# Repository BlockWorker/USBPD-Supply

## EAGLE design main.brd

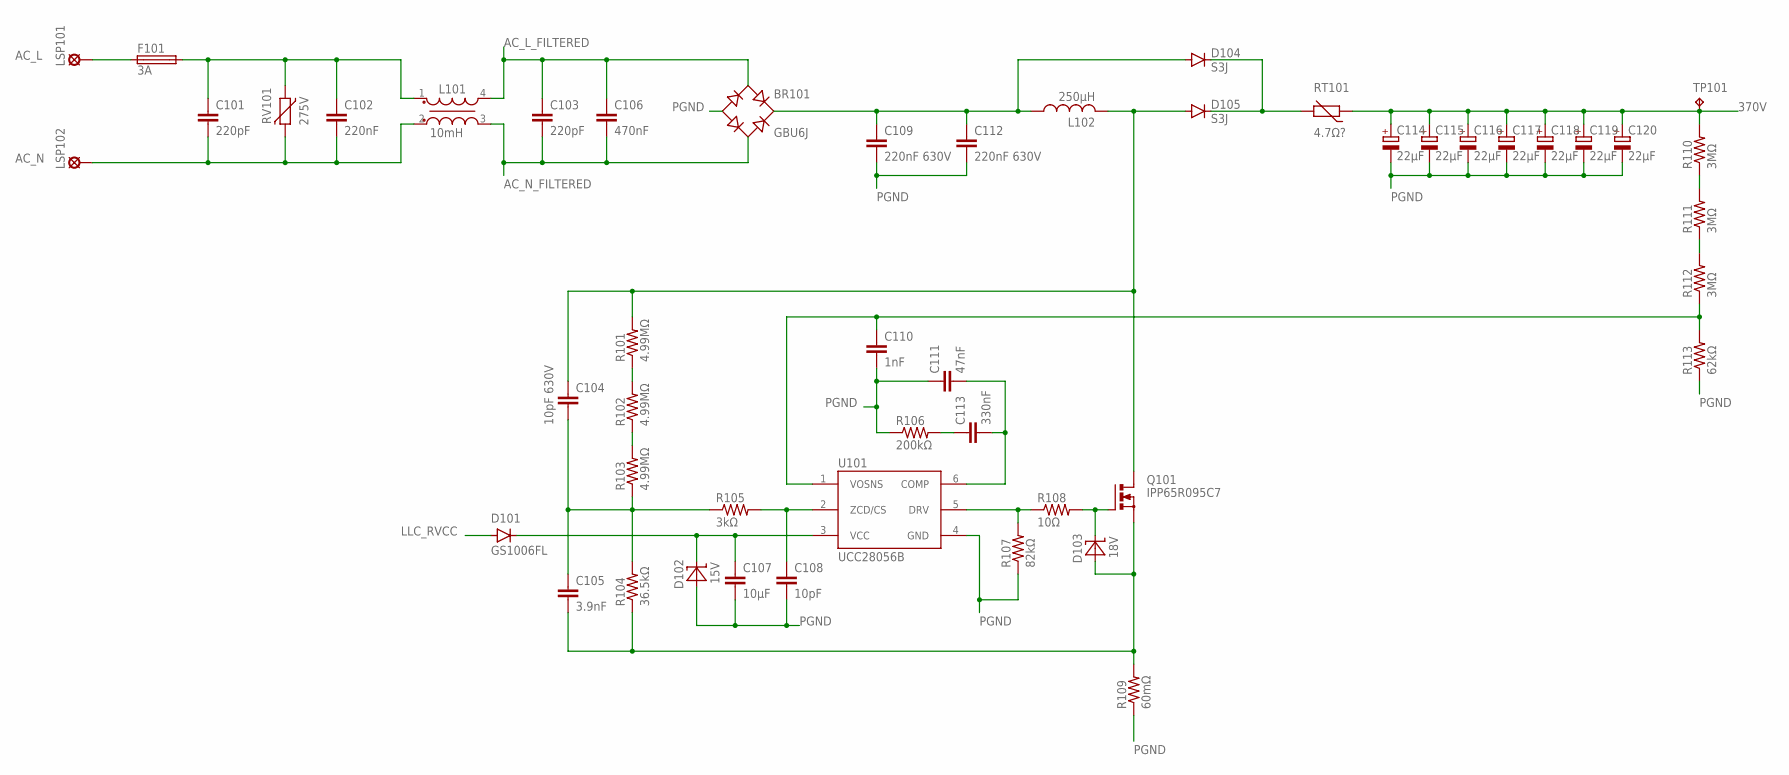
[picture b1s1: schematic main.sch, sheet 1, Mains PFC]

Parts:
BR101: GBU6J; GBU6
C101, C103: 220pF; C-10MM-TH
C102: 220nF; WCAP-FTX2-220N
C104: 10pF 630V; C1206
C105: 3.9nF; C0603
C106: 470nF; WCAP-FTX2-470N
C107: 10µF; C0805
C108: 10pF; C0603
C109, C112: 220nF 630V; C1812
C110: 1nF; C0603
C111: 47nF; C0603
C113: 330nF; C0603
C114, C115, C116, C117, C118, C119, C120: 22µF; E5-12.5
D101: GS1006FL; SOD123FL
D102: 15V; SOD123
D103: 18V; SOD123
D104, D105: S3J; SMC
F101: 3A; MRF_FUSE
L101: 10mH; WE-CMB_M
L102: 250µH; ATCA-08
LSP101: AC_L; LSP13
LSP102: AC_N; LSP13
Q101: IPP65R095C7; TO220BV-HS1
R101, R102, R103: 4.99MΩ; R1206
R104: 36.5kΩ; R0603
R105: 3kΩ; R0603
R106: 200kΩ; R0603
R107: 82kΩ; R0603
R108: 10Ω; R0603
R109: 60mΩ; R1206
R110, R111, R112: 3MΩ; R1206
R113: 62kΩ; R0603
RT101: 4.7Ω?; R-5
RV101: 275V; B72207S0271
TP101: RCU-0(J); TP_0603_JOINED
U101: UCC28056B; SOT23-6L

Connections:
370V: C114.+, C115.+, C116.+, C117.+, C118.+, C119.+, C120.+, R110.2, RT101.1, TP101.1; also elsewhere on the board
AC_L: F101.1, LSP101.MP
AC_L_FILTERED: BR101.2 (AC1), C103.1, C106.1, L101.4; also elsewhere on the board
AC_L_FUSED: C101.1, C102.1, F101.2, L101.1, RV101.1
AC_N: C101.2, C102.2, L101.2, LSP102.MP, RV101.2
AC_N_FILTERED: BR101.3 (AC2), C103.2, C106.2, L101.3; also elsewhere on the board
AC_RECTIFIED: BR101.4 (+), C109.1, C112.1, D104.A, L102.1
LLC_RVCC: D101.A; also elsewhere on the board
PFC_COMP: C111.2, C113.2, U101.6 (COMP)
PFC_COMP_INT: C113.1, R106.2
PFC_CS: C105.2, D103.A, Q101.S, R104.1, R109.2
PFC_DRV: R107.2, R108.1, U101.5 (DRV)
PFC_DRV_R: D103.C, Q101.G, R108.2
PFC_OUT_RAW: D104.C, D105.C, RT101.2
PFC_SW_NODE: C104.1, D105.A, L102.2, Q101.D, R101.2
PFC_VCC: C107.1, D101.C, D102.C, U101.3 (VCC)
PFC_VOSNS: C110.1, R112.1, R113.2, U101.1 (VOSNS)
PFC_VOSNS_RB: R111.1, R112.2
PFC_VOSNS_RT: R110.1, R111.2
PFC_ZCD/CS: C108.1, R105.2, U101.2 (ZCD/CS)
PFC_ZCD/CS_RAW: C104.2, C105.1, R103.1, R104.2, R105.1
PFC_ZCD_RB: R102.1, R103.2
PFC_ZCD_RT: R101.1, R102.2
PGND: BR101.1 (-), C107.2, C108.2, C109.2, C110.2, C111.1, C112.2, C114.-, C115.-, C116.-, C117.-, C118.-, C119.-, C120.-, D102.A, R106.1, R107.1, R109.1, R113.1, U101.4 (GND); also elsewhere on the board

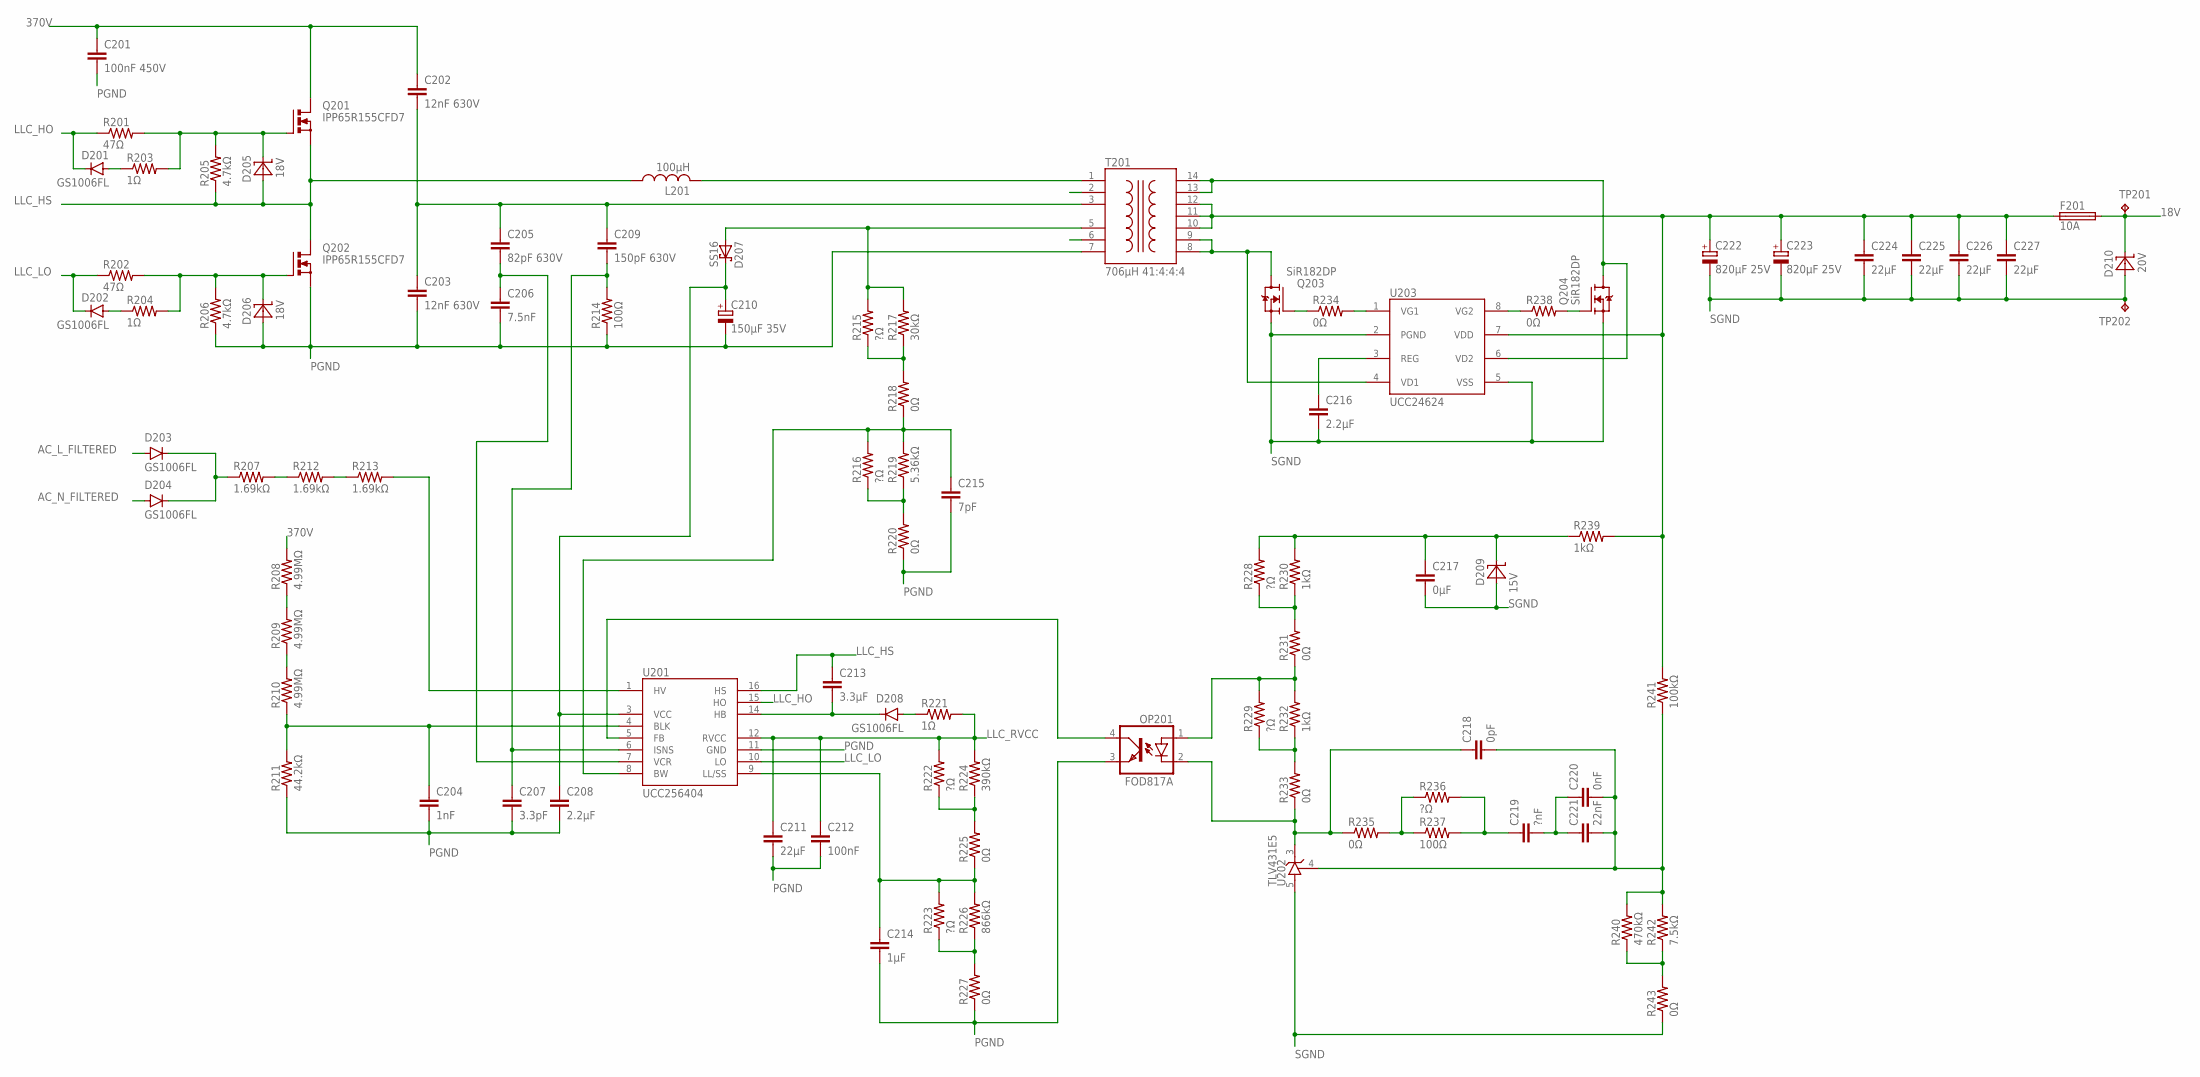
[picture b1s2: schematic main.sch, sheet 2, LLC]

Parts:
C201: 100nF 450V; C1206
C202, C203: 12nF 630V; C1210
C204: 1nF; C0603
C205: 82pF 630V; C1206
C206: 7.5nF; C0603
C207: 3.3pF; C0603
C208, C216: 2.2µF; C0805
C209: 150pF 630V; C1206
C210: 150µF 35V; PANASONIC_E
C211, C224, C225, C226, C227: 22µF; C0805
C212: 100nF; C0603
C213: 3.3µF; C0805
C214: 1µF; C0603
C215: 7pF; C0603
C217: 0µF; C0603
C218: 0pF; C0603
C219: ?nF; C0603
C220: 0nF; C0603
C221: 22nF; C0603
C222, C223: 820µF 25V; E5-10,5
D201, D202, D203, D204, D208: GS1006FL; SOD123FL
D205, D206: 18V; SOD123
D207: SS16; DO-214AC
D209: 15V; SOD123
D210: 20V; SOD123
F201: 10A; MRF_FUSE
L201: 100µH; HCTI-1MM
OP201: FOD817A; DIP4
Q201, Q202: IPP65R155CFD7; TO220BV-HS1
Q203, Q204: SiR182DP; POWERPAK-SO8
R201, R202: 47Ω; R0603
R203, R204, R221: 1Ω; R0603
R205, R206: 4.7kΩ; R0603
R207, R212, R213: 1.69kΩ; R1206
R208, R209, R210: 4.99MΩ; R1206
R211: 44.2kΩ; R0603
R214: 100Ω; R1206
R215, R216, R222, R223, R228, R229, R236: ?Ω; R0603
R217: 30kΩ; R0603
R218, R220, R225, R227, R231, R233, R234, R235, R238, R243: 0Ω; R0603
R219: 5.36kΩ; R0603
R224: 390kΩ; R0603
R226: 866kΩ; R0603
R230, R232, R239: 1kΩ; R0603
R237: 100Ω; R0603
R240: 470kΩ; R0603
R241: 100kΩ; R0603
R242: 7.5kΩ; R0603
T201: 706µH 41:4:4:4; ETD29/16/10-H
TP201, TP202: RCU-0(J); TP_0603_JOINED
U201: UCC256404; SOIC16-NO2,13
U202: TLV431E5; SOT23-5L
U203: UCC24624; SOIC8

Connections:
18V: D210.C, F201.2, TP201.1; also elsewhere on the board
370V: C201.1, C202.1, Q201.D, R208.2; also elsewhere on the board
AC_L_FILTERED: D203.A; also elsewhere on the board
AC_N_FILTERED: D204.A; also elsewhere on the board
LLC_AUX: D207.A, R215.2, R217.2, T201.5
LLC_BLK: C204.1, R210.1, R211.2, U201.4 (BLK)
LLC_BLK_RB: R209.1, R210.2
LLC_BLK_RT: R208.1, R209.2
LLC_BW: C215.1, R216.2, R218.1, R219.2, U201.8 (BW)
LLC_BW_RB: R216.1, R219.1, R220.2
LLC_BW_RT: R215.1, R217.1, R218.2
LLC_FB: OP201.4 (COL), U201.5 (FB)
LLC_FB_COMP: C219.1, R236.2, R237.2
LLC_FB_COMPC: C219.2, C220.1, C221.1
LLC_FB_COMPR: R235.2, R236.1, R237.1
LLC_FB_OPA: OP201.1 (A), R229.2, R231.1, R232.2
LLC_FB_OPAP: C217.1, D209.C, R228.2, R230.2, R239.1
LLC_FB_OPAR: R228.1, R230.1, R231.2
LLC_FB_OPBR: R229.1, R232.1, R233.2
LLC_FB_OPK: C218.1, OP201.2 (C), R233.1, R235.1, U202.3 (C)
LLC_FB_VREF: C218.2, C220.2, C221.2, R240.2, R241.1, R242.2, U202.4 (R)
LLC_FB_VREFR: R240.1, R242.1, R243.2
LLC_HB: C213.2, D208.C, U201.14 (HB)
LLC_HB_FEED: D208.A, R221.1
LLC_HO: D201.C, R201.1, U201.15 (HO)
LLC_HO_DIS: D201.A, R203.1
LLC_HO_R: D205.C, Q201.G, R201.2, R203.2, R205.2
LLC_HS: C213.1, D205.A, L201.1, Q201.S, Q202.D, R205.1, U201.16 (HS)
LLC_HV: R213.2, U201.1 (HV)
LLC_HV_RB: R212.2, R213.1
LLC_HV_RECT: D203.C, D204.C, R207.1
LLC_HV_RT: R207.2, R212.1
LLC_ISNS: C207.1, C209.2, R214.2, U201.6 (ISNS)
LLC_LL/SS: C214.1, R223.2, R225.1, R226.2, U201.9 (LL/SS)
LLC_LL_RB: R223.1, R226.1, R227.2
LLC_LL_RT: R222.1, R224.1, R225.2
LLC_LO: D202.C, R202.1, U201.10 (LO)
LLC_LO_DIS: D202.A, R204.1
LLC_LO_R: D206.C, Q202.G, R202.2, R204.2, R206.2
LLC_OUT: C222.+, C223.+, C224.1, C225.1, C226.1, C227.1, F201.1, R239.2, R241.2, T201.10, T201.11, T201.12, U203.7 (VDD)
LLC_PRI_IN: L201.2, T201.1
LLC_PRI_OUT: C202.2, C203.1, C205.1, C209.1, T201.3
LLC_RVCC: C211.1, C212.1, R221.2, R222.2, R224.2, U201.12 (RVCC); also elsewhere on the board
LLC_SR_REG: C216.1, U203.3 (REG)
LLC_SR_VD1: Q203.5-8 (D), T201.8, T201.9, U203.4 (VD1)
LLC_SR_VD2: Q204.5-8 (D), T201.13, T201.14, U203.6 (VD2)
LLC_SR_VG1: R234.2, U203.1 (VG1)
LLC_SR_VG1_R: Q203.4 (G), R234.1
LLC_SR_VG2: R238.1, U203.8 (VG2)
LLC_SR_VG2_R: Q204.4 (G), R238.2
LLC_VCC: C208.1, C210.+, D207.C, U201.3 (VCC)
LLC_VCR: C205.2, C206.1, U201.7 (VCR)
PGND: C201.2, C203.2, C204.2, C206.2, C207.2, C208.2, C210.-, C211.2, C212.2, C214.2, C215.2, D206.A, OP201.3 (EMIT), Q202.S, R206.1, R211.1, R214.1, R220.1, R227.1, T201.7, U201.11 (GND); also elsewhere on the board
PRI_DUMMY_1: T201.2
PRI_DUMMY_2: T201.6
SGND: C216.2, C217.2, C222.-, C223.-, C224.2, C225.2, C226.2, C227.2, D209.A, D210.A, Q203.1 (S), Q203.2 (S), Q203.3 (S), Q204.1 (S), Q204.2 (S), Q204.3 (S), R243.1, TP202.1, U202.5 (A), U203.2 (PGND), U203.5 (VSS); also elsewhere on the board

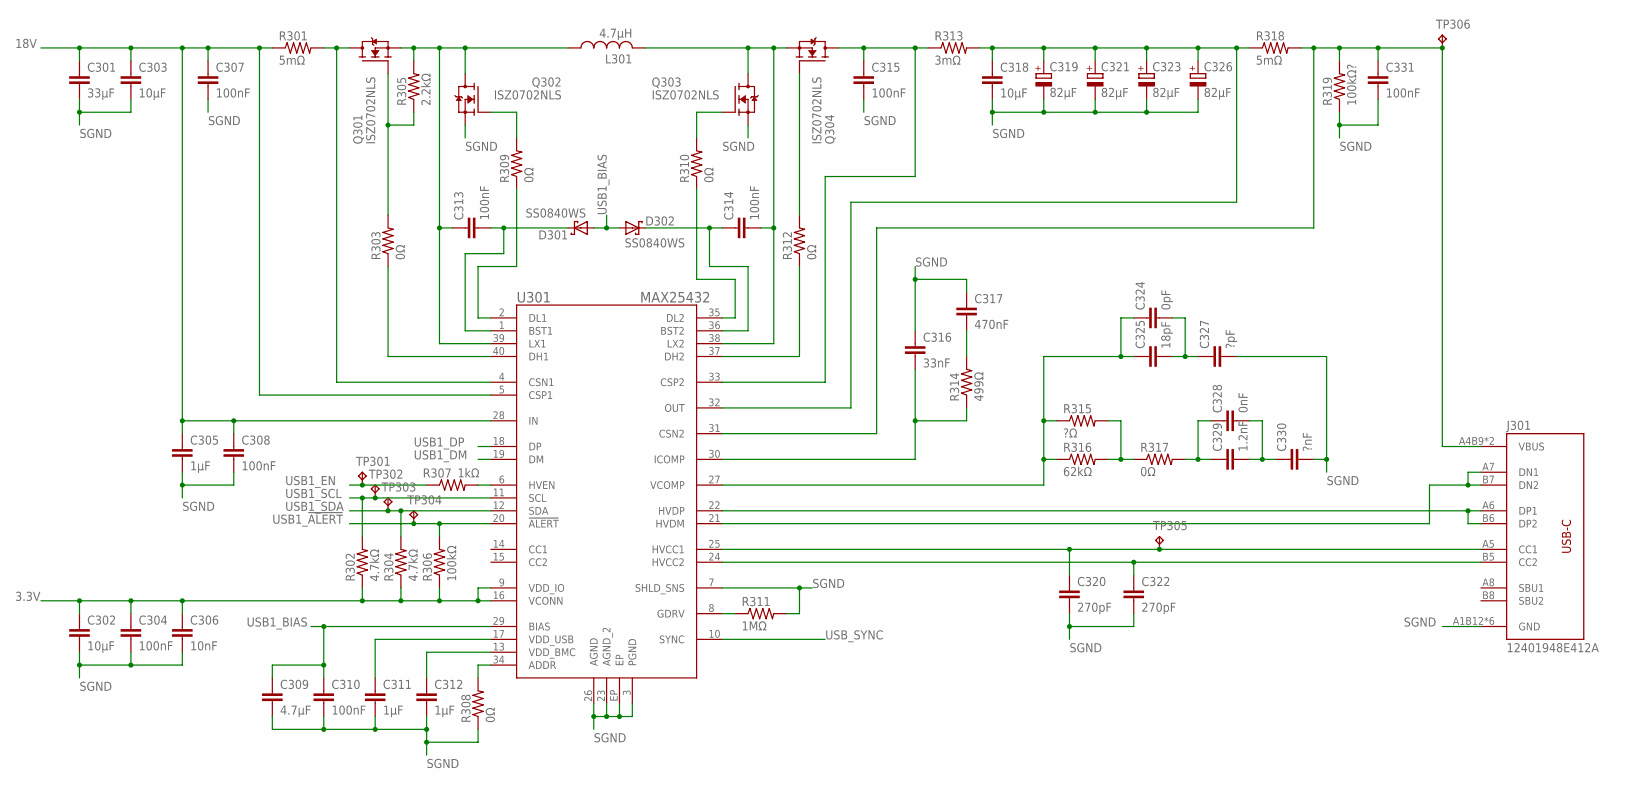
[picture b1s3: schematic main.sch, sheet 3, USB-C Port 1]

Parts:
C301: 33µF; C1206
C302, C303, C318: 10µF; C0805
C304, C307, C308, C310, C313, C314, C315, C331: 100nF; C0603
C305, C311, C312: 1µF; C0603
C306: 10nF; C0603
C309: 4.7µF; C0603
C316: 33nF; C0603
C317: 470nF; C0603
C319, C321, C323, C326: 82µF; E3,5-8
C320, C322: 270pF; C0603
C324: 0pF; C0603
C325: 18pF; C0603
C327: ?pF; C0603
C328: 0nF; C0603
C329: 1.2nF; C0603
C330: ?nF; C0603
D301, D302: SS0840WS; SOD323
J301: 12401948E412A
L301: 4.7µH; B82559B*A016
Q301, Q302, Q303, Q304: ISZ0702NLS; TSDSON-8
R301, R318: 5mΩ; R0805
R302, R304: 4.7kΩ; R0603
R303, R308, R309, R310, R312, R317: 0Ω; R0603
R305: 2.2kΩ; R0603
R306: 100kΩ; R0603
R307: 1kΩ; R0603
R311: 1MΩ; R0603
R313: 3mΩ; R0805
R314: 499Ω; R0603
R315: ?Ω; R0603
R316: 62kΩ; R0603
R319: 100kΩ?; R0603
TP301, TP302, TP303, TP304, TP305, TP306: RCU-0(J); TP_0603_JOINED
U301: MAX25432; TQFN-40

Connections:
3.3V: C302.1, C304.1, C306.1, R302.1, R304.1, R306.1, U301.9 (VDD_IO), U301.16 (VCONN); also elsewhere on the board
18V: C301.1, C303.1, C305.1, C307.1, C308.1, R301.1, U301.5 (CSP1), U301.28 (IN); also elsewhere on the board
SGND: C301.2, C302.2, C303.2, C304.2, C305.2, C306.2, C307.2, C308.2, C309.2, C310.2, C311.2, C312.2, C315.2, C316.1, C317.1, C318.2, C319.-, C320.2, C321.-, C322.2, C323.-, C326.-, C327.2, C330.2, C331.2, J301.A1B12 (GND), J301.B1A12 (GND), J301.M1 (GND), J301.M2 (GND), J301.M3 (GND), J301.M4 (GND), Q302.1 (S), Q302.2 (S), Q302.3 (S), Q303.1 (S), Q303.2 (S), Q303.3 (S), R308.1, R311.2, R319.1, U301.3 (PGND), U301.7 (SHLD_SNS), U301.23 (AGND_2), U301.26 (AGND), U301.EP; also elsewhere on the board
USB1_!ALERT: R306.2, TP304.1, U301.20 (!ALERT); also elsewhere on the board
USB1_ADDR: R308.2, U301.34 (ADDR)
USB1_BIAS: C309.1, C310.1, D301.2 (A), D302.2 (A), U301.29 (BIAS)
USB1_BST1: C313.2, D301.1 (C), U301.1 (BST1)
USB1_BST2: C314.1, D302.1 (C), U301.36 (BST2)
USB1_CC1: C320.1, J301.A5 (CC1), TP305.1, U301.25 (HVCC1)
USB1_CC2: C322.1, J301.B5 (CC2), U301.24 (HVCC2)
USB1_CSN1: Q301.5-8 (D), R301.2, U301.4 (CSN1)
USB1_CSP2: C315.1, Q304.5-8 (D), R313.1, U301.33 (CSP2)
USB1_DH1: R303.1, U301.40 (DH1)
USB1_DH1_R: Q301.4 (G), R303.2, R305.1
USB1_DH2: R312.1, U301.37 (DH2)
USB1_DH2_R: Q304.4 (G), R312.2
USB1_DL1: R309.1, U301.2 (DL1)
USB1_DL1_R: Q302.4 (G), R309.2
USB1_DL2: R310.1, U301.35 (DL2)
USB1_DL2_R: Q303.4 (G), R310.2
USB1_DM: U301.19 (DM); also elsewhere on the board
USB1_DP: U301.18 (DP); also elsewhere on the board
USB1_EN: R307.1, TP301.1; also elsewhere on the board
USB1_GDRV: R311.1, U301.8 (GDRV)
USB1_HVDM: J301.A7 (DN1), J301.B7 (DN2), U301.21 (HVDM)
USB1_HVDP: J301.A6 (DP1), J301.B6 (DP2), U301.22 (HVDP)
USB1_HVEN: R307.2, U301.6 (HVEN)
USB1_ICOMP: C316.2, R314.1, U301.30 (ICOMP)
USB1_ICOMP_R: C317.2, R314.2
USB1_LX1: C313.1, L301.1, Q301.1 (S), Q301.2 (S), Q301.3 (S), Q302.5-8 (D), R305.2, U301.39 (LX1)
USB1_LX2: C314.2, L301.2, Q303.5-8 (D), Q304.1 (S), Q304.2 (S), Q304.3 (S), U301.38 (LX2)
USB1_OUT: C318.1, C319.+, C321.+, C323.+, C326.+, R313.2, R318.1, U301.32 (OUT)
USB1_SCL: R302.2, TP302.1, U301.11 (SCL); also elsewhere on the board
USB1_SDA: R304.2, TP303.1, U301.12 (SDA); also elsewhere on the board
USB1_VBUS: C331.1, J301.A4B9 (VBUS), J301.B4A9 (VBUS), R318.2, R319.2, TP306.1, U301.31 (CSN2)
USB1_VCOMP: C324.1, C325.1, R315.1, R316.1, U301.27 (VCOMP)
USB1_VCOMP_CPI: C324.2, C325.2, C327.1
USB1_VCOMP_CZI: C328.2, C329.2, C330.1
USB1_VCOMP_R: C328.1, C329.1, R317.2
USB1_VCOMP_RI: R315.2, R316.2, R317.1
USB1_VDD_BMC: C312.1, U301.13 (VDD_BMC)
USB1_VDD_USB: C311.1, U301.17 (VDD_USB)
USB_SYNC: U301.10 (SYNC); also elsewhere on the board

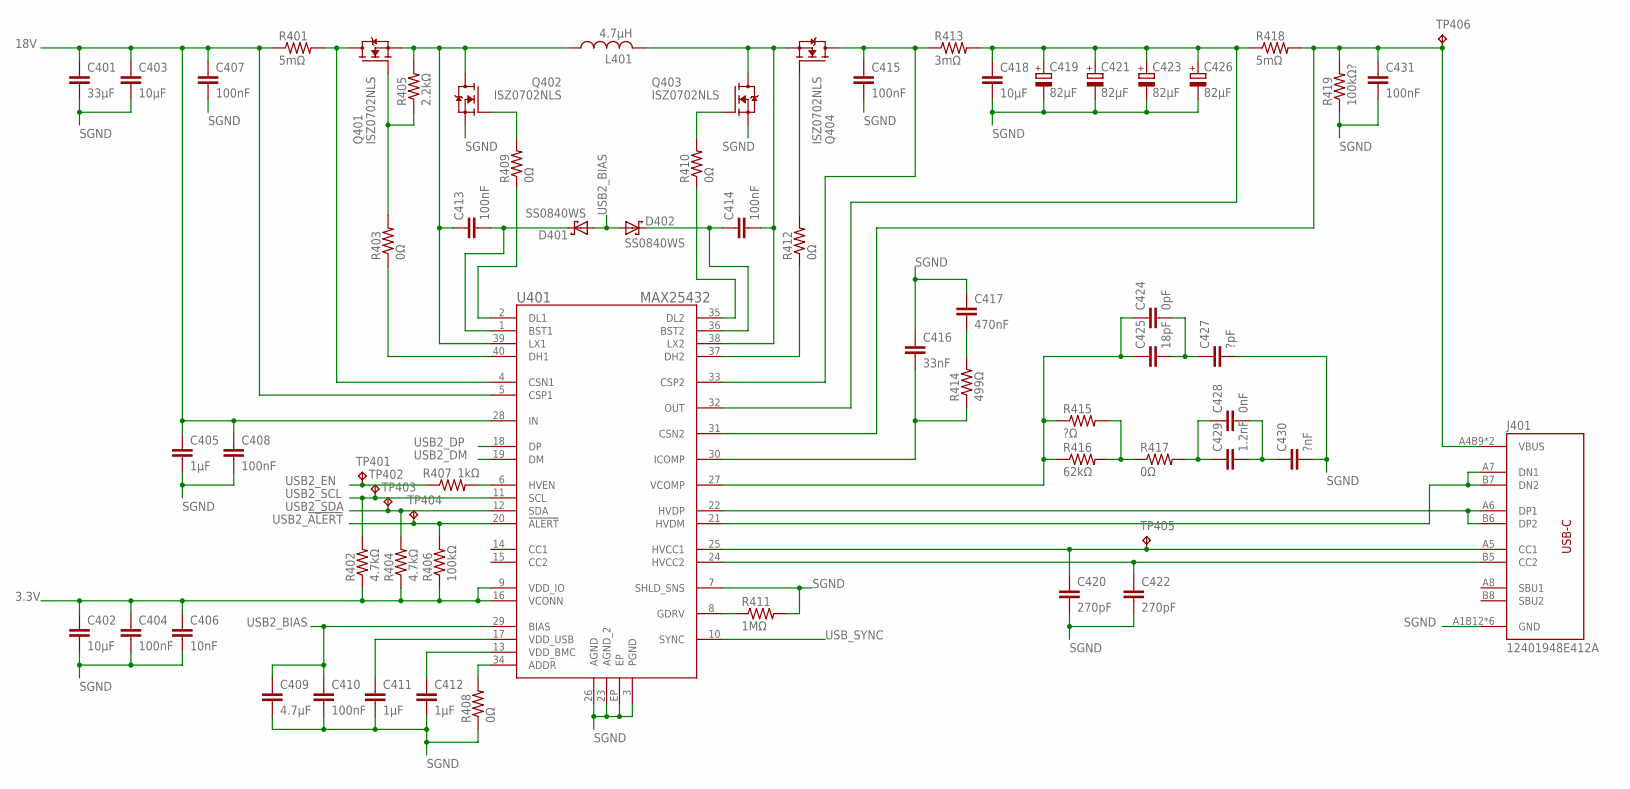
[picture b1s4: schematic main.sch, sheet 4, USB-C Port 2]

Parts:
C401: 33µF; C1206
C402, C403, C418: 10µF; C0805
C404, C407, C408, C410, C413, C414, C415, C431: 100nF; C0603
C405, C411, C412: 1µF; C0603
C406: 10nF; C0603
C409: 4.7µF; C0603
C416: 33nF; C0603
C417: 470nF; C0603
C419, C421, C423, C426: 82µF; E3,5-8
C420, C422: 270pF; C0603
C424: 0pF; C0603
C425: 18pF; C0603
C427: ?pF; C0603
C428: 0nF; C0603
C429: 1.2nF; C0603
C430: ?nF; C0603
D401, D402: SS0840WS; SOD323
J401: 12401948E412A
L401: 4.7µH; B82559B*A016
Q401, Q402, Q403, Q404: ISZ0702NLS; TSDSON-8
R401, R418: 5mΩ; R0805
R402, R404: 4.7kΩ; R0603
R403, R408, R409, R410, R412, R417: 0Ω; R0603
R405: 2.2kΩ; R0603
R406: 100kΩ; R0603
R407: 1kΩ; R0603
R411: 1MΩ; R0603
R413: 3mΩ; R0805
R414: 499Ω; R0603
R415: ?Ω; R0603
R416: 62kΩ; R0603
R419: 100kΩ?; R0603
TP401, TP402, TP403, TP404, TP405, TP406: RCU-0(J); TP_0603_JOINED
U401: MAX25432; TQFN-40

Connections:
3.3V: C402.1, C404.1, C406.1, R402.1, R404.1, R406.1, U401.9 (VDD_IO), U401.16 (VCONN); also elsewhere on the board
18V: C401.1, C403.1, C405.1, C407.1, C408.1, R401.1, U401.5 (CSP1), U401.28 (IN); also elsewhere on the board
SGND: C401.2, C402.2, C403.2, C404.2, C405.2, C406.2, C407.2, C408.2, C409.2, C410.2, C411.2, C412.2, C415.2, C416.1, C417.1, C418.2, C419.-, C420.2, C421.-, C422.2, C423.-, C426.-, C427.2, C430.2, C431.2, J401.A1B12 (GND), J401.B1A12 (GND), J401.M1 (GND), J401.M2 (GND), J401.M3 (GND), J401.M4 (GND), Q402.1 (S), Q402.2 (S), Q402.3 (S), Q403.1 (S), Q403.2 (S), Q403.3 (S), R408.1, R411.2, R419.1, U401.3 (PGND), U401.7 (SHLD_SNS), U401.23 (AGND_2), U401.26 (AGND), U401.EP; also elsewhere on the board
USB2_!ALERT: R406.2, TP404.1, U401.20 (!ALERT); also elsewhere on the board
USB2_ADDR: R408.2, U401.34 (ADDR)
USB2_BIAS: C409.1, C410.1, D401.2 (A), D402.2 (A), U401.29 (BIAS)
USB2_BST1: C413.2, D401.1 (C), U401.1 (BST1)
USB2_BST2: C414.1, D402.1 (C), U401.36 (BST2)
USB2_CC1: C420.1, J401.A5 (CC1), TP405.1, U401.25 (HVCC1)
USB2_CC2: C422.1, J401.B5 (CC2), U401.24 (HVCC2)
USB2_CSN1: Q401.5-8 (D), R401.2, U401.4 (CSN1)
USB2_CSP2: C415.1, Q404.5-8 (D), R413.1, U401.33 (CSP2)
USB2_DH1: R403.1, U401.40 (DH1)
USB2_DH1_R: Q401.4 (G), R403.2, R405.1
USB2_DH2: R412.1, U401.37 (DH2)
USB2_DH2_R: Q404.4 (G), R412.2
USB2_DL1: R409.1, U401.2 (DL1)
USB2_DL1_R: Q402.4 (G), R409.2
USB2_DL2: R410.1, U401.35 (DL2)
USB2_DL2_R: Q403.4 (G), R410.2
USB2_DM: U401.19 (DM); also elsewhere on the board
USB2_DP: U401.18 (DP); also elsewhere on the board
USB2_EN: R407.1, TP401.1; also elsewhere on the board
USB2_GDRV: R411.1, U401.8 (GDRV)
USB2_HVDM: J401.A7 (DN1), J401.B7 (DN2), U401.21 (HVDM)
USB2_HVDP: J401.A6 (DP1), J401.B6 (DP2), U401.22 (HVDP)
USB2_HVEN: R407.2, U401.6 (HVEN)
USB2_ICOMP: C416.2, R414.1, U401.30 (ICOMP)
USB2_ICOMP_R: C417.2, R414.2
USB2_LX1: C413.1, L401.1, Q401.1 (S), Q401.2 (S), Q401.3 (S), Q402.5-8 (D), R405.2, U401.39 (LX1)
USB2_LX2: C414.2, L401.2, Q403.5-8 (D), Q404.1 (S), Q404.2 (S), Q404.3 (S), U401.38 (LX2)
USB2_OUT: C418.1, C419.+, C421.+, C423.+, C426.+, R413.2, R418.1, U401.32 (OUT)
USB2_SCL: R402.2, TP402.1, U401.11 (SCL); also elsewhere on the board
USB2_SDA: R404.2, TP403.1, U401.12 (SDA); also elsewhere on the board
USB2_VBUS: C431.1, J401.A4B9 (VBUS), J401.B4A9 (VBUS), R418.2, R419.2, TP406.1, U401.31 (CSN2)
USB2_VCOMP: C424.1, C425.1, R415.1, R416.1, U401.27 (VCOMP)
USB2_VCOMP_CPI: C424.2, C425.2, C427.1
USB2_VCOMP_CZI: C428.2, C429.2, C430.1
USB2_VCOMP_R: C428.1, C429.1, R417.2
USB2_VCOMP_RI: R415.2, R416.2, R417.1
USB2_VDD_BMC: C412.1, U401.13 (VDD_BMC)
USB2_VDD_USB: C411.1, U401.17 (VDD_USB)
USB_SYNC: U401.10 (SYNC); also elsewhere on the board

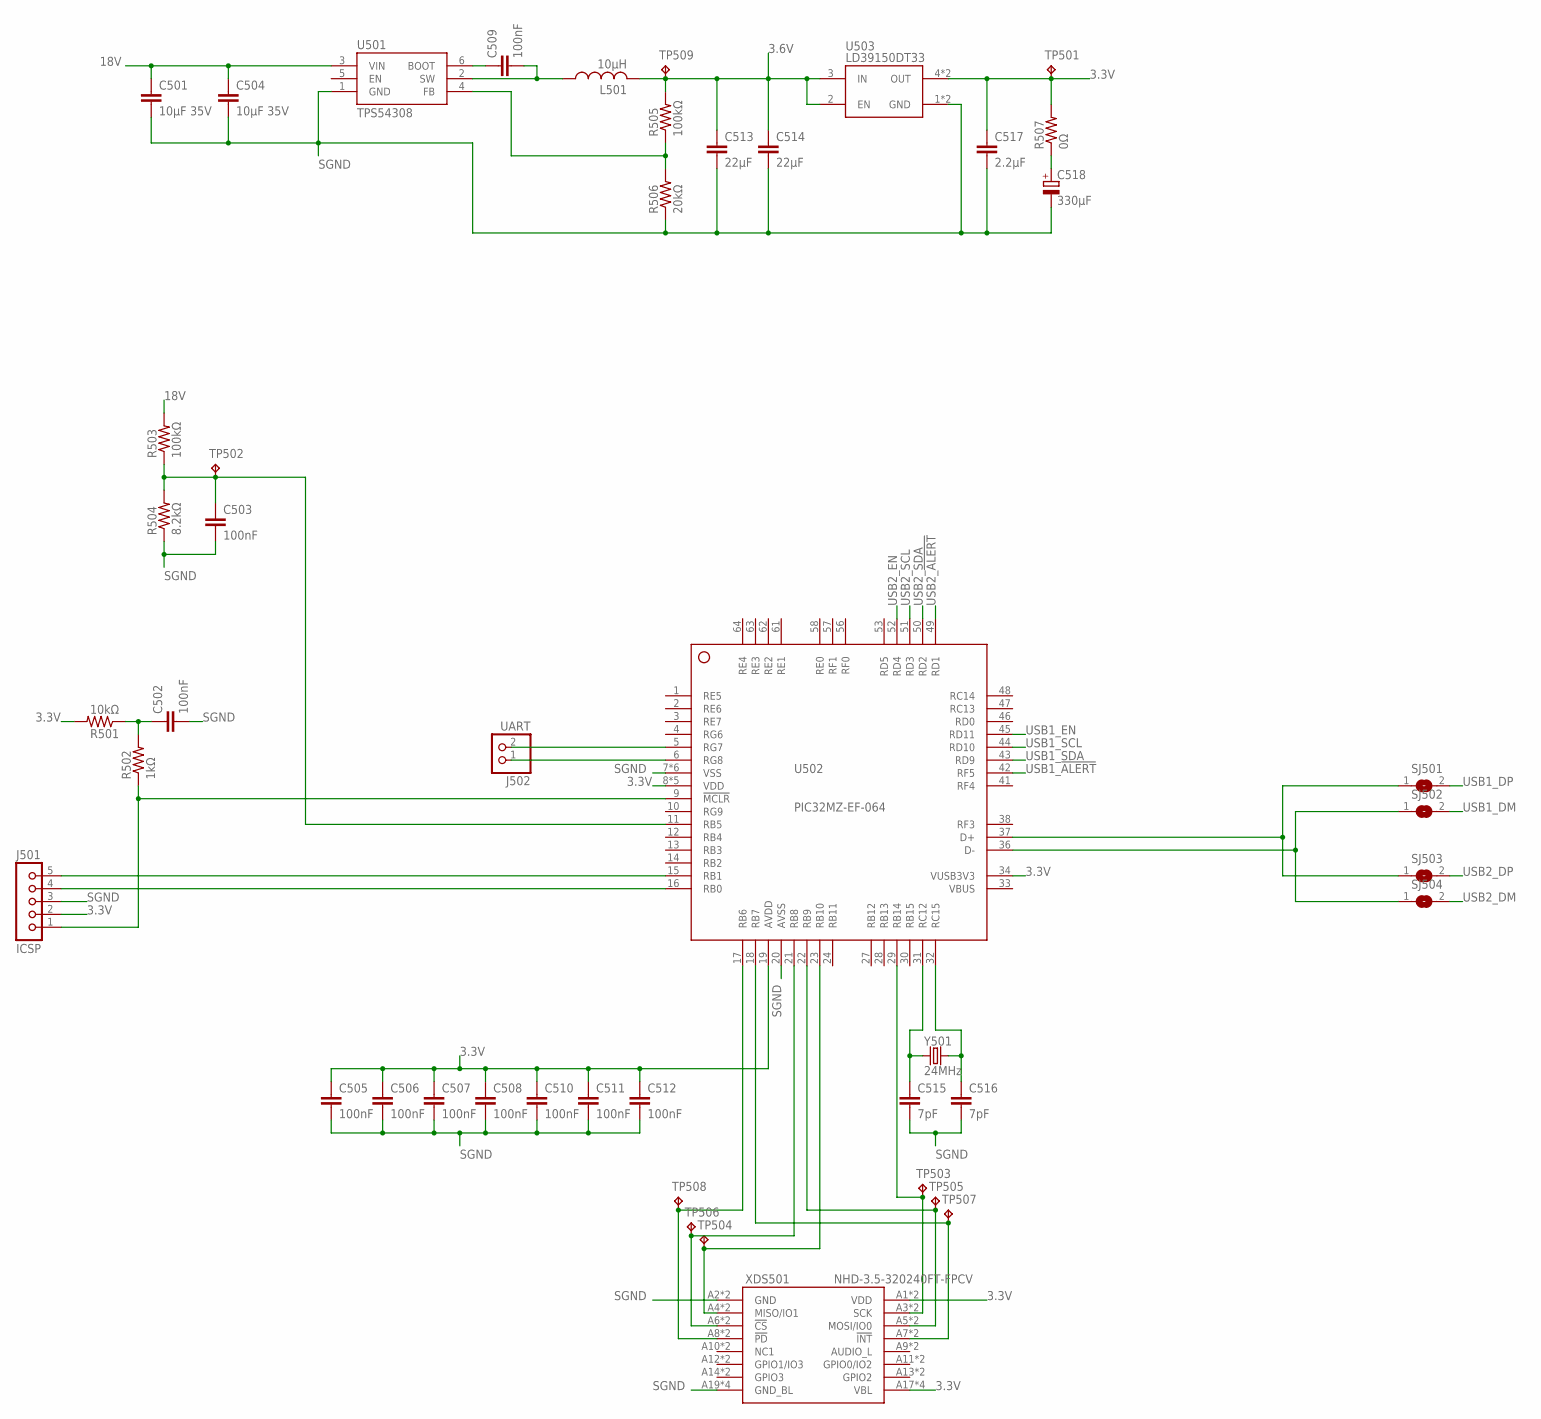
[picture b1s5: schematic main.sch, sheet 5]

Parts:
C501, C504: 10µF 35V; C1206
C502, C503, C505, C506, C507, C508, C509, C510, C511, C512: 100nF; C0603
C513, C514: 22µF; C0805
C515, C516: 7pF; C0603
C517: 2.2µF; C0805
C518: 330µF; PANASONIC_D
J501: ICSP; 5PIN-1.27
J502: UART; 1X02
L501: 10µH; RLB0912
R501: 10kΩ; R0603
R502: 1kΩ; R0603
R503, R505: 100kΩ; R0603
R504: 8.2kΩ; R0603
R506: 20kΩ; R0603
R507: 0Ω; R0603
SJ501, SJ502, SJ503, SJ504: SJ
TP501, TP502, TP503, TP504, TP505, TP506, TP507, TP508, TP509: RCU-0(J); TP_0603_JOINED
U501: TPS54308; SOT23-6L
U502: PIC32MZ-EF-064; TQFP64-10X10X1MM
U503: LD39150DT33; DFN6
XDS501: NHD-3.5-320240FT-FPCV; FFC3A20-20
Y501: 24MHz; XRCGB

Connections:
3.3V: C505.1, C506.1, C507.1, C508.1, C510.1, C511.1, C512.1, C517.1, J501.2, R501.2, R507.2, TP501.1, U502.8 (VDD), U502.19 (AVDD), U502.26 (VDD), U502.34 (VUSB3V3), U502.39 (VDD), U502.54 (VDD), U502.60 (VDD), U503.4 (OUT), U503.5 (OUT), XDS501.A1 (VDD), XDS501.A17 (VBL), XDS501.A18 (VBL), XDS501.B1 (VDD), XDS501.B17 (VBL), XDS501.B18 (VBL); also elsewhere on the board
3.3V_BULKR: C518.+, R507.1
3.6V: C513.1, C514.1, L501.2, R505.2, TP509.1, U503.2 (EN), U503.3 (IN)
18V: C501.1, C504.1, R503.2, U501.3 (VIN); also elsewhere on the board
LCD_!CS: TP506.1, U502.21 (RB8), XDS501.A6 (!CS), XDS501.B6 (!CS)
LCD_!INT: TP507.1, U502.18 (RB7), XDS501.A7 (!INT), XDS501.B7 (!INT)
LCD_!PD: TP508.1, U502.17 (RB6), XDS501.A8 (!PD), XDS501.B8 (!PD)
LCD_MISO: TP504.1, U502.23 (RB10), XDS501.A4 (MISO/IO1), XDS501.B4 (MISO/IO1)
LCD_MOSI: TP505.1, U502.22 (RB9), XDS501.A5 (MOSI/IO0), XDS501.B5 (MOSI/IO0)
LCD_SCK: TP503.1, U502.29 (RB14), XDS501.A3 (SCK), XDS501.B3 (SCK)
PIC_!MCLR: J501.1, R502.1, U502.9 (!MCLR)
PIC_!MCLR!_FILTER: C502.1, R501.1, R502.2
PIC_D+: SJ501.1, SJ503.1, U502.37 (D+)
PIC_D-: SJ502.1, SJ504.1, U502.36 (D-)
PIC_OSC1: C515.1, U502.31 (RC12), Y501.1
PIC_OSC2: C516.1, U502.32 (RC15), Y501.3 (2)
PIC_PGEC: J501.5, U502.15 (RB1)
PIC_PGED: J501.4, U502.16 (RB0)
PIC_UART_RX: J502.1, U502.6 (RG8)
PIC_UART_TX: J502.2, U502.5 (RG7)
PIC_VIN_SENSE: C503.1, R503.1, R504.2, TP502.1, U502.11 (RB5)
PRELIN_BOOT: C509.1, U501.6 (BOOT)
PRELIN_FB: R505.1, R506.2, U501.4 (FB)
PRELIN_SW: C509.2, L501.1, U501.2 (SW)
SGND: C501.2, C502.2, C503.2, C504.2, C505.2, C506.2, C507.2, C508.2, C510.2, C511.2, C512.2, C513.2, C514.2, C515.2, C516.2, C517.2, C518.-, J501.3, R504.1, R506.1, U501.1 (GND), U502.7 (VSS), U502.20 (AVSS), U502.25 (VSS), U502.35 (VSS), U502.40 (VSS), U502.55 (VSS), U502.59 (VSS), U503.1 (GND), U503.T (GND), XDS501.A2 (GND), XDS501.A19 (GND_BL), XDS501.A20 (GND_BL), XDS501.B2 (GND), XDS501.B19 (GND_BL), XDS501.B20 (GND_BL); also elsewhere on the board
USB1_!ALERT: U502.42 (RF5); also elsewhere on the board
USB1_DM: SJ502.2; also elsewhere on the board
USB1_DP: SJ501.2; also elsewhere on the board
USB1_EN: U502.45 (RD11); also elsewhere on the board
USB1_SCL: U502.44 (RD10); also elsewhere on the board
USB1_SDA: U502.43 (RD9); also elsewhere on the board
USB2_!ALERT: U502.49 (RD1); also elsewhere on the board
USB2_DM: SJ504.2; also elsewhere on the board
USB2_DP: SJ503.2; also elsewhere on the board
USB2_EN: U502.52 (RD4); also elsewhere on the board
USB2_SCL: U502.51 (RD3); also elsewhere on the board
USB2_SDA: U502.50 (RD2); also elsewhere on the board

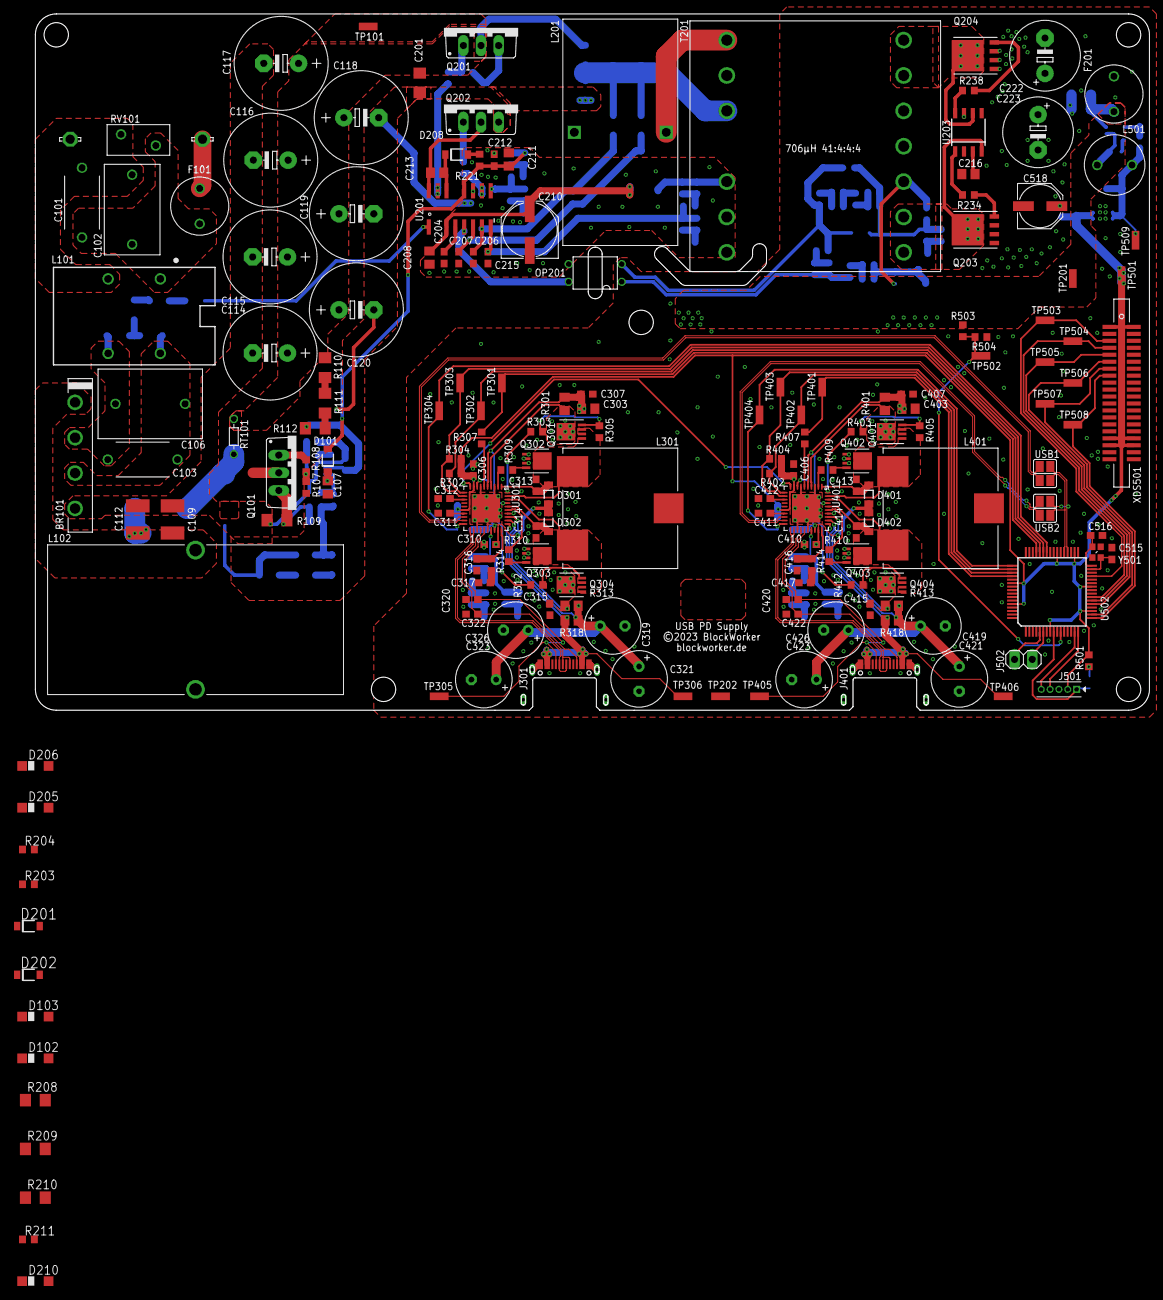
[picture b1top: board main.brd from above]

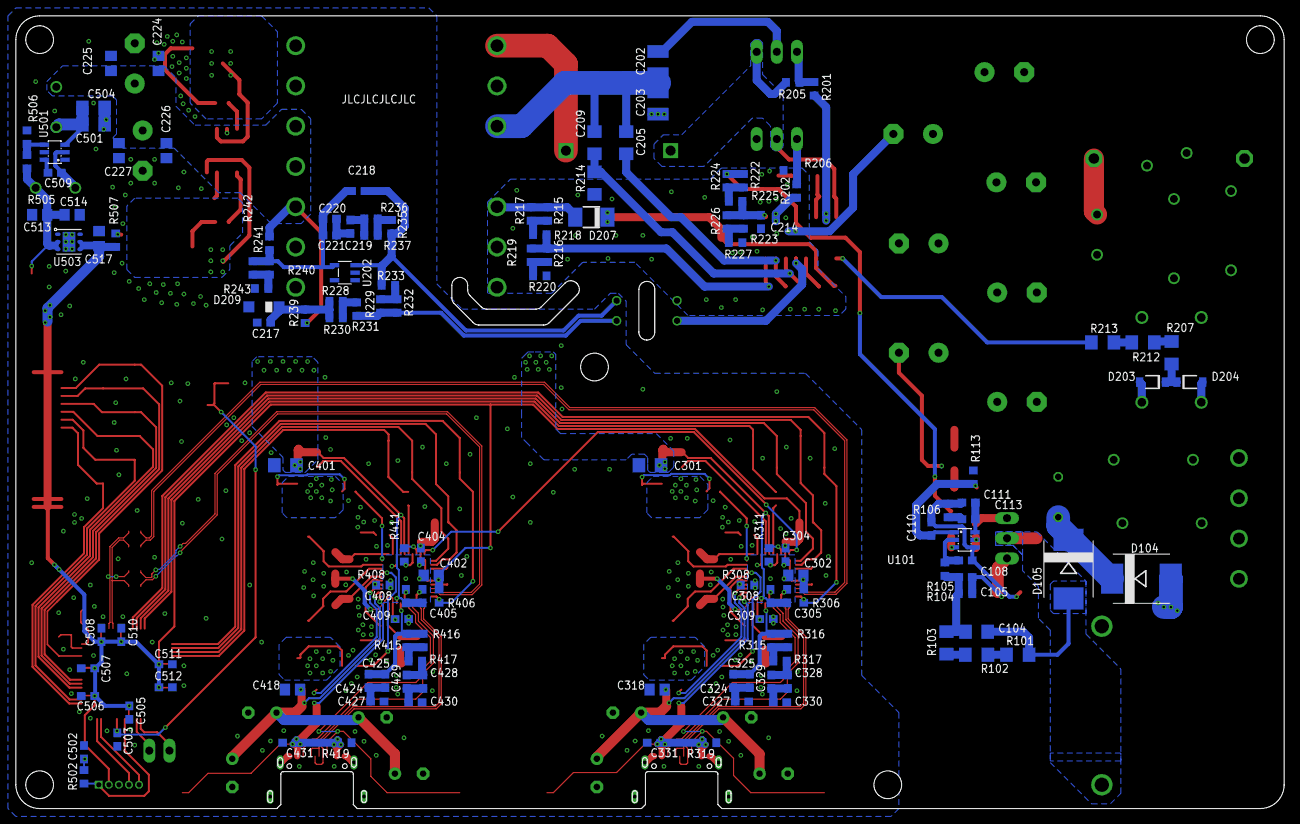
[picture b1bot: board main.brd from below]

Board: 2 copper layers, 160.0 x 100.0 mm, 318 parts (132 on the bottom side), 175 nets.

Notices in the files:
adapter/USBPD-Adapter.X/mcc_generated_files/pin_manager.h:
(c) 2020 Microchip Technology Inc. and its subsidiaries. You may use this
firmware/src/config/default/peripheral/gpio/plib_gpio.h:
Copyright (C) 2019 Microchip Technology Inc. and its subsidiaries.
adapter.brd:
©2023 BlockWorker
parts and their libraries:
Eagle_WE-CMB: Copyright: Würth Elektronik
COPYRIGHT: Copyright (C) 2023 Ultra Librarian. All rights reserved.
